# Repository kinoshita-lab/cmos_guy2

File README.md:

# CMOS野郎2
## 説明
CMOS野郎2は、シュミットトリガインバータ(TC7W14FU)を使った発振器と、スピーカーを組み合わせた、電池で動くシンプルな楽器です。
ステレオラインアウトもあります。

初代CMOS野郎(初代CMOS野郎
https://github.com/kinoshita-lab/cmos-guy )を基板化&小型化したものです。

<image src="./image.JPG" width="400">

## 基本的な使い方
- 電池を入れると動きます。**向きに気をつけてください。** 使わない時は電池をはずしてください。
- あまり奥まで電池を入れると、抜くのが大変なので途中くらいにしておくとよいです。
- ツマミを回すと、ピッチが変わります。

## 応用的な使い方
- 回路がむき出しになっているので、あちこち触ってみると面白いです。
    - ツマミの裏辺りを触ると微妙にピッチが変わります。上手くやるとビブラートもできます。
    - スピーカーの穴を指でふさいだりすると、微妙にフィルターがかかります。
- 複数使うと、うなり(beat)が作れて面白いかもしれません。
- ミキサーに差すと、とりあえずPAつながってる？とかわかって便利かもしれません。

## 交換が必要な部品
電池は **CR2032** を使って下さい。

## 回路

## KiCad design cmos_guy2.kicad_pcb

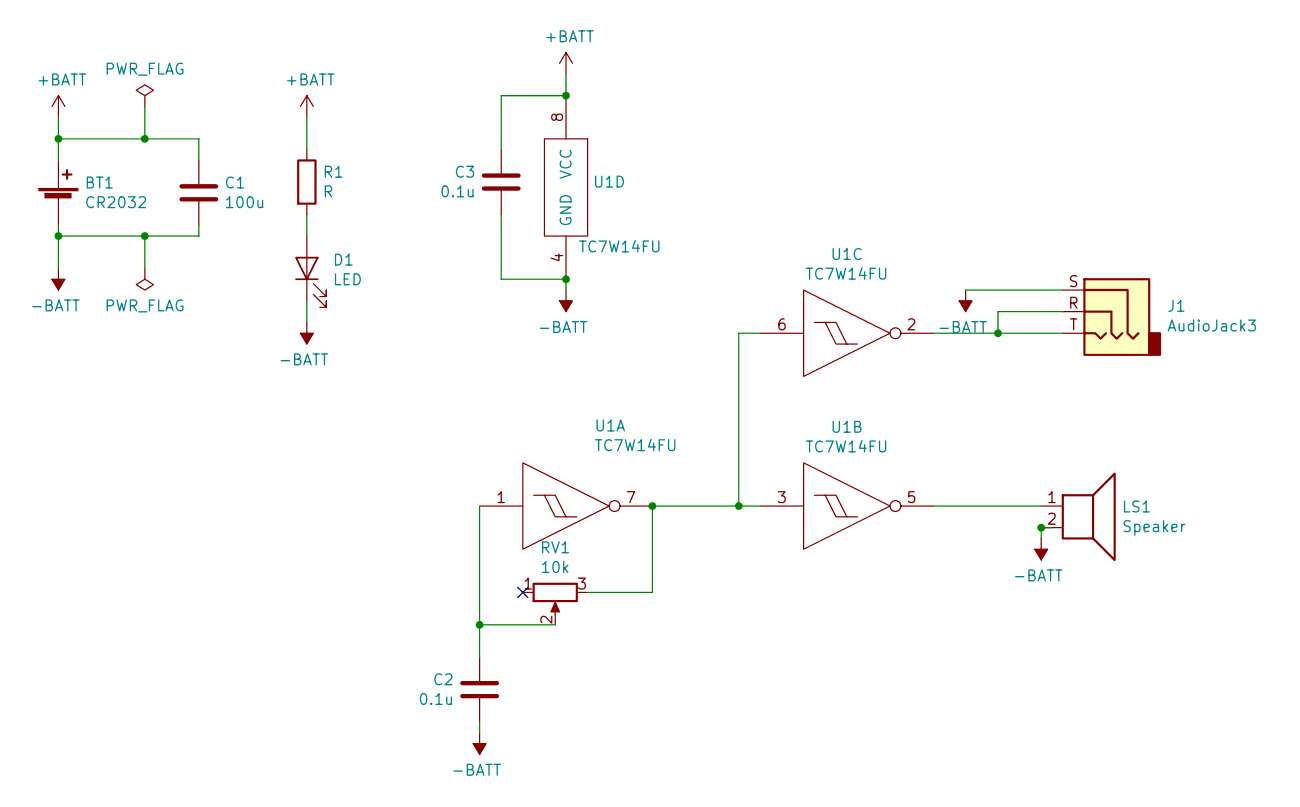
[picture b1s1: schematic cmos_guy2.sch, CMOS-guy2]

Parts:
BT1: CR2032; Battery_Holder_CR2032_Akiduki
C1: 100u; C_1206_HandSoldering
C2, C3: 0.1u; C_0603_HandSoldering
D1: LED; LED_0603_HandSoldering
J1: AudioJack3; stereo_3.5mm_stereo_uxcell_thruhole
LS1: Speaker; UGCM0603APE_Akiduki_Small_Speaker_6.7mm
R1: R; R_0603_HandSoldering
RV1: 10k; POT_TOCOS_GF063P1
U1: TC7W14FU; SSOP-8_2.95x2.8mm_Pitch0.65mm

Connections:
+BATT: BT1.1 (+), C1.1, C3.1, R1.1, U1.8 (VCC)
-BATT: BT1.2 (-), C1.2, C2.2, C3.2, D1.1 (K), J1.S, LS1.2, U1.4 (GND)
unnamed: C2.1, RV1.2, U1.1 (A)
unnamed: D1.2 (A), R1.2
unnamed: J1.R, J1.T, U1.2 (3Y)
unnamed: LS1.1, U1.5 (2Y)
unnamed: RV1.3, U1.3 (2A), U1.6 (3A), U1.7 (Y)

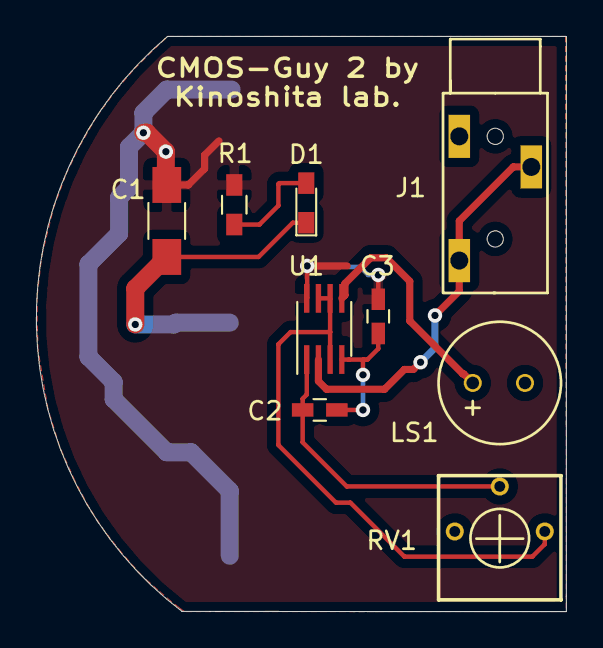
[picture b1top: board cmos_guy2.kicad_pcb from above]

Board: 2 copper layers, 29.4 x 32.0 mm, 10 parts (1 on the bottom side), 7 nets.

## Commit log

2019-04-26 add files
2019-04-26 add documentation
2019-04-26 tweak documentation
2019-09-15 add pdf manual
2019-09-15 add pdf manual(formerly failed)
2020-05-16 Create LICENSE
